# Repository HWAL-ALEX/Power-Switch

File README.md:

# Power-Switch

# Introduction
I use this repo to share all my design about power switch.

# Liste 
- POWER SWITCH 12V 10A

Have fun
HWAL

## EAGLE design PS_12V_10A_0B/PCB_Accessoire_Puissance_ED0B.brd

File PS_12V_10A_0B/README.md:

# Power switch 12v 10a
## Description
it is high side power switch 

## Caracteristic
there are three connectors for three signals
- 12V INPUT (Power)
- 12V OUTPUT (Power)
- COMMAND

## Dimension
10mm x 20mm

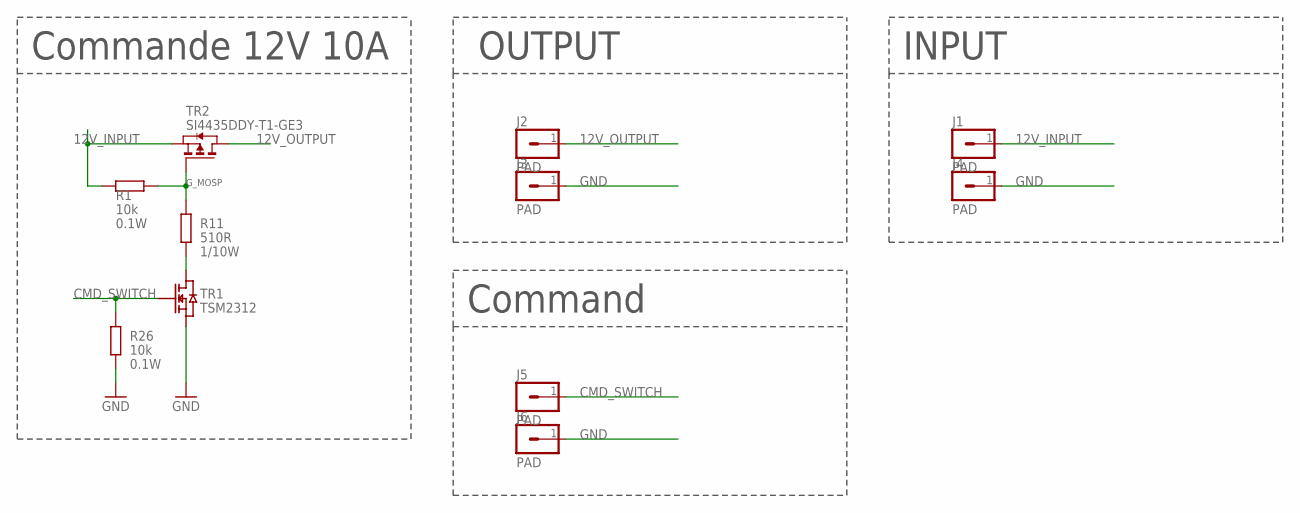
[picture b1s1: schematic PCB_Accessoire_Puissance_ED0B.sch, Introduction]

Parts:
J1, J2, J3, J4, J5, J6: PAD; PAD_2X3MM
R1, R26: 10k; R0603
R11: 510R; R0603
TR1: TSM2312; SOT23
TR2: SI4435DDY-T1-GE3; SOIC8

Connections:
12V_INPUT: J1.1, R1.2, TR2.1 (S), TR2.2 (S), TR2.3 (S)
12V_OUTPUT: J2.1, TR2.5 (D), TR2.6 (D), TR2.7 (D), TR2.8 (D)
CMD_SWITCH: J5.1, R26.2, TR1.1 (G)
GND: J3.1, J4.1, J6.1, R26.1, TR1.2 (S)
G_MOSP: R1.1, R11.2, TR2.4 (G)
unnamed: R11.1, TR1.3 (D)

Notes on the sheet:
Commande 12V 10A
OUTPUT
INPUT
Command

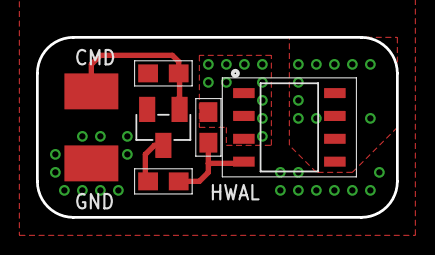
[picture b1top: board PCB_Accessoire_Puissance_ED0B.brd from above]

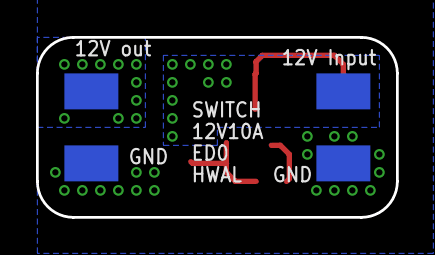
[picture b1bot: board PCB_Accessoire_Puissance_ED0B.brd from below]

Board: 2 copper layers, 20.0 x 10.0 mm, 11 parts (4 on the bottom side), 6 nets.

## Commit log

2020-08-11 add Eagle FIle
2020-08-11 File Hardware
2020-08-11 Update dimension
2020-08-11 Add schematic.PDF
